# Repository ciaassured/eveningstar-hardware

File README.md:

# Eveningstar Hardware

Eveningstar is a gateway between a Morningstar MeterBus network and a standard Ethernet/IP network. It connects to the MeterBus port of a Morningstar solar charge controller or other compatible device, making the bus accessible over Ethernet for monitoring, automation, and control.

The hardware is built around an ESP32-C6 and divided into two galvanically isolated sections:

* A MeterBus interface, powered from the connected Morningstar device.
* An ESP32 and Ethernet interface, powered from its own DC input.

This isolation keeps the MeterBus network and the Morningstar device's ground separate from the rest of the system, which prevents ground loops through the MeterBus cable and stops fault currents from flowing across it. The ESP32 side can be powered from the same battery system as the charge controller or from a separate supply, even when the two operate at different voltages.

MeterBus communication is half-duplex and open-drain. The interface includes a Schmitt-trigger receive path and transient-voltage-suppression clamps to improve reliability when cables are routed through electrically noisy environments.

## Specifications

| | |
| --- | --- |
| Processor | ESP32-C6-WROOM-1-N8 module: Wi-Fi 6, Bluetooth LE, and IEEE 802.15.4, with 8 MB flash and an on-board antenna |
| Storage | 256 MB SPI NAND flash (GD5F2GM7) |
| Real-time clock | 32.768 kHz crystal |
| Ethernet | 10/100 Mbit/s, WIZnet W5500 with a hardware TCP/IP stack, RJ45 jack with integrated magnetics |
| MeterBus | RJ11 (6P6C) jack to the Morningstar MeterBus port |
| USB | USB-C to the ESP32-C6's native USB, for flashing, a serial console, and JTAG debugging; it does not power the board |
| Debug | Unpopulated 2.54 mm 2×3 header with serial, reset, and boot pins |
| Power input | 8–40 V DC through a 3.81 mm pluggable terminal block, ESP32 side |
| MeterBus supply | Powered by the Morningstar device through the MeterBus port, up to the 15.5 V Morningstar specifies, MeterBus side |
| Isolation | ISO6721 digital isolator between the two sides, rated 3000 V rms withstand and 450 V rms working voltage (basic isolation, UL 1577); only data crosses it |
| Operating temperature | −30 °C to +85 °C, from component ratings |
| Board size | 81.2 × 71.6 mm |

## Protection

* **Power input:** a 1 A fuse, a series Schottky diode against reverse polarity, and a 40 V TVS diode that clamps surges. The TVS diode sets the 40 V upper limit, well within the 80 V rating of the LMR38020S converter behind it.
* **Brown-out:** the ESP32 is held in reset until the converter reports that the 3.3 V rail is in regulation.
* **MeterBus:** galvanic isolation, since the MeterBus side is powered by the Morningstar device and shares no power or ground with the rest of the board. Its supply has a series Schottky diode against reverse polarity and a 17 V TVS diode, and the data line has a TVS clamp for positive and negative spikes.
* **USB:** ESD protection on the data lines. VBUS is not connected to any power rail, so the board cannot draw power from USB or feed power back into it.
* **Ethernet:** the jack's integrated magnetics transformer-couple the data pairs, and its shield is connected to ground only through a 1 nF, 2 kV capacitor, so the Ethernet cable carries no DC ground current.

The ratings above come from component datasheets. The board has not been independently tested or certified for isolation, surge immunity, or its temperature range.

## Installation

* **Power:** connect 8–40 V DC to the terminal block, observing the + and − markings on the bottom of the board. Add a Fuse the positive supply with a 1 A fuse close to the power source, and use wiring rated to carry at least 1 A continuously. This fuse protects the wiring in case of a short circuit. Choose a fuse that is appropriately rated for the system's voltages and currents.
* **MeterBus:** connect the RJ11 jack to the Morningstar device's MeterBus port using a standard straight through cable. The MeterBus side takes its power from that port. The outer two pins on each side of the 6P6C connector are shorted which means it is possible to use a four pin cable, but six pin is recommended.
* **Ethernet:** connect a standard Ethernet cable. The board is not powered over Ethernet. Note that this device does not support Auto-MDIX so a crossover cable may be needed in some cases if the other device also doesn't support auto Auto-MDIX.

> [!WARNING]
> Do not leave USB connected while the system is in service. USB ground is connected directly to the power input's negative terminal, so a connected USB host that is grounded elsewhere creates a second ground path. Current can then flow through the board's unfused ground and the USB cable, which can damage equipment or start a fire. Use USB only for flashing or debugging, and disconnect it afterwards.

## Debugging

### USB

The USB-C port connects straight to the ESP32-C6's native USB; there is no USB-to-serial chip in between. The chip's built-in USB Serial/JTAG controller gives a serial console, flashing, and JTAG debugging over one cable. The controller is part of the chip's hardware and is supported by its ROM bootloader, so it works on a blank module with no bootloader or firmware in flash, and the chip can enter download mode over USB by itself.

Firmware can still make the USB device disappear, by reconfiguring the USB pins, disabling the controller, or entering a sleep mode. If that happens, force the chip into its ROM download mode through the debug header, as below.

Remember that USB is for flashing and debugging only; see the warning under [Installation](#installation).

### Debug header

The unpopulated 2.54 mm 2×3 header, marked DEBUG, breaks out the ESP32's first serial port and its reset and boot pins:

| Pin | Label | Signal |
| --- | --- | --- |
| 1 | RST | ESP32 reset (EN), active low |
| 2 | 3V3 | Board 3.3 V rail, through jumper J_3V3 |
| 3 | TX | ESP32 UART0 transmit; connect to the adapter's receive |
| 4 | GND | Ground |
| 5 | RX | ESP32 UART0 receive; connect to the adapter's transmit |
| 6 | BOOT | ESP32 GPIO9; held low at reset, it enters ROM download mode |

Use it to flash over serial, including the bootloader, or to recover a board whose firmware has disabled native USB: hold BOOT low while releasing RST, and the chip starts in ROM download mode. Programmers that drive both pins can do this automatically.

When using the header, power the board with an external DC supply through its normal power input and on-board converter, and remove jumper J_3V3 so that the programmer's 3.3 V cannot backfeed the converter.

If the converter's power-good signal holds the reset line low while you are trying to flash or debug through the header, remove jumper J_RST as well; it connects the power-good signal to the ESP32's reset line.

J_3V3 and J_RST are 0603 0 Ω resistors beside the header, fitted at assembly and marked on the silkscreen.

## Resources

* Schematics, board drawings, 3D models, renders, and JLCPCB production files for the current hardware revision are attached to the [latest release](https://github.com/ciaassured/eveningstar-hardware/releases/latest).
* To order assembled boards, follow [`docs/jlcpcb_order.md`](docs/jlcpcb_order.md).
* Firmware is maintained separately in the [eveningstar-firmware](https://github.com/ciaassured/eveningstar-firmware) repository.
* The KiCad project and its build, review, and fabrication workflow are documented in [`pcb/README.md`](pcb/README.md).

## Disclaimer

This project is experimental and is not affiliated with or endorsed by Morningstar Corporation.

Use it at your own risk when interfacing with battery and solar equipment.

### AI Assistance

Portions of this project were created or modified using AI-assisted tools. AI-generated suggestions may be incomplete or incorrect and must not be treated as engineering certification.

Before manufacturing or using this hardware, independently review the schematics, PCB layout, component ratings, isolation boundaries, and fabrication outputs. Appropriate electrical, thermal, safety, and regulatory testing must also be performed.

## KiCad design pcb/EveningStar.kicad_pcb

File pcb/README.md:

# Eveningstar PCB

This directory contains the KiCad project for the Eveningstar PCB.

## Reproducibility Goal

The PCB should remain openable from this repository in the future, even if
external KiCad libraries, plugin indexes, vendor APIs, or downloaded data
sources disappear or change shape.

The rule of thumb is:

- Project-specific symbols, footprints, and 3D models should be committed under
  `pcb/lib`.
- Third-party libraries that are used by the board should be vendored into this
  repository, not referenced through a local KiCad plugin path.
- External tools are acceptable when they are sufficiently pinned and
  recoverable. KiCad itself is provided through the root Nix flake and locked by
  `flake.lock`.
- KiCad stock symbols are referenced through `KICAD_SYMBOL_DIR`, which is set by
  the Nix tooling to the flake-pinned KiCad package.

If a part needs local customization, copy the symbol, footprint, or model into a
project-owned library and reference that copy.

## Nix Workflow

The root flake owns the lock file and imports the PCB-specific Nix module from
`pcb/nix`. Use the flake from the repository root.

Open a shell with the pinned KiCad version:

```sh
nix develop
```

The dev shell includes KiCad plus the project helper scripts. Inside the shell,
the scripts are available as `eveningstar-*` commands.

Entering the development shell installs or updates the repo's pre-commit hook
for the current clone. It can also be installed explicitly from the shell:

```sh
lefthook install
```

Git does not automatically trust and execute hooks from cloned repositories.
Entering `nix develop` is the developer's explicit trust step: the shell uses
the Nix-provided Lefthook to sync `.git/hooks`, so Nix remains the only tooling
dependency. Lefthook then runs the same Nix-backed check suite used by CI.

## Checks

Run every automated check:

```sh
nix run .#checks
# or, inside nix develop:
eveningstar-checks
```

The aggregate command runs all checks even if an earlier one fails, then exits
non-zero if any failed. It is the entry point used by Lefthook and GitHub
Actions.

The individual checks remain available for diagnosing a failure.

### ERC and DRC

Run KiCad ERC and DRC, including warnings:

```sh
nix run .#drc
# or, inside nix develop:
eveningstar-drc
```

This writes `reports/erc.rpt` and `reports/drc.rpt`, prints both reports, and
exits non-zero if ERC or DRC reports violations.

### Repo-local KiCad references

Check for references to local, non-repo KiCad libraries or model paths:

```sh
nix run .#kicad-locality
# or, inside nix develop:
eveningstar-kicad-locality
```

This fails on absolute paths, KiCad third-party plugin variables, missing
repo-local 3D models, footprint library table entries outside `${KIPRJMOD}`, and
symbol library table entries outside `${KIPRJMOD}` or pinned `KICAD_SYMBOL_DIR`.

### Saved copper-zone fills

Check that every copper zone contains saved fill data on each of its layers:

```sh
nix run .#zones-filled
# or, inside nix develop:
eveningstar-zones-filled
```

After any board edit that can affect copper geometry, open the board in the
pinned KiCad PCB Editor, press <kbd>B</kbd> to refill all zones, and save before
committing. Production plotting uses the fills stored in the board, so this is
required even if DRC passes. The automated check detects absent saved fills; it
cannot prove that existing fills are current for the latest board edits.

### Vendored subtree drift

Check that the vendored JLCPCB subtree has not been edited directly:

```sh
nix run .#subtree-drift
# or, inside nix develop:
eveningstar-subtree-drift
```

This verifies `pcb/lib/JLCPCB-Kicad-Library` still matches the recorded subtree
squash commit and rejects uncommitted changes under that subtree.

## Publish Tools

Publish tools generate the complete artifact set for one hardware revision. They
are available through Nix, but are intentionally not run by Lefthook or CI.

Generate publish artifacts for the current checkout:

```sh
nix build --max-jobs auto .#publish
# or, to also link the result at reports/publish:
nix run .#publish
# inside nix develop:
eveningstar-publish
```

The output is exactly the set of GitHub release assets, in one flat directory
because releases hold no folders:

| File                         | Contents                                              |
| ---------------------------- | ----------------------------------------------------- |
| `EveningStar-gerbers.zip`    | Gerber and drill files for JLCPCB                     |
| `EveningStar-bom.csv`        | JLCPCB bill of materials                              |
| `EveningStar-cpl.csv`        | JLCPCB component placement list                       |
| `EveningStar-netlist.ipc`    | IPC-D-356 netlist for electrical test                 |
| `EveningStar-schematic.pdf`  | every schematic sheet                                 |
| `EveningStar-board.pdf`      | composite front and back views, then each layer       |
| `EveningStar-step.zip`       | STEP model of the assembled board, for enclosure CAD  |
| `EveningStar.glb`            | browser-optimized 3D model                            |
| `EveningStar-render-*.png`   | top, bottom, front, back, and isometric renders       |
| `EveningStar-turntable.webp` | the [turntable animation](#turntable-animation)       |
| `SHA256SUMS`                 | checksums of every other file                         |

Names carry no version, so `releases/latest/download/<name>` always links the
newest board, and the output depends only on the source rather than on the tag
it is released under. The production files are the `.#production` payload, which
uses the same names; the Toolkit's `designators.csv` is left out of both because
it only repeats the BOM. The per-sheet and per-layer SVGs are review artifacts
rather than release assets, built by `nix run .#review`.

`nix build` exposes the Nix store output through `result`; the command form also links that immutable output at
`reports/publish`. Because this is a derivation of the filtered PCB source and
pinned publishing tools, unchanged outputs are reused from the local Nix store
and can be shared through the configured Cachix cache. Release metadata and
changelog generation can be added to this same artifact contract without
changing the review workflow.

Generate only the JLCPCB production payload:

```sh
nix build .#production
# or, to also link the result at reports/production:
nix run .#production
# inside nix develop:
eveningstar-production
```

The production payload contains the Gerber/drill archive, BOM, placement list,
and IPC-D-356 netlist, under the same names as the GitHub release. Its settings
pin the Fabrication Toolkit 5.3.1 JLCPCB placement translations used for V1. The
build runs DRC and schematic-parity validation, then plots the zone fills
committed in the KiCad board without refilling them. Fill and save zones in the
pinned KiCad editor after relevant design changes; plotting the reviewed stored
fills avoids nondeterministic polygon decomposition between independent KiCad
processes. Project-specific corrections live as hidden `FT Rotation Offset`
fields on the affected KiCad footprints; update them only after checking
component pin 1 orientation against the datasheet and assembly preview. The
Toolkit's built-in rotations match footprint names by pattern, such as
`^SOT-23`, and are meant for KiCad's standard footprints, so EasyEDA-named
footprints that happen to match, such as D7's
`SOT-23-3_L3.0-W1.7-P0.95-LS2.9-BR`, carry a 180° offset that cancels them.
Through-hole parts are placed at the centre of their pads unless `FT Origin` is
`Anchor`, which RJ2 uses because JLCPCB's model for it sits on the footprint
anchor. U1's SOT-89 counts as through-hole because its tab has plated holes, so
it needs the same. Generated timestamps, ZIP entry metadata, permissions, and
file order are normalized for reproducible builds. The Toolkit source revision
is pinned by the root `flake.lock` alongside KiCad and the rest of the
toolchain. KiCad provides the underlying fabrication exporters; the pinned
Toolkit is retained for its JLCPCB-specific component-origin and rotation
translations and for compatibility with the production process used for the
original board.

Production files are build artifacts and are not committed. Local output is
ignored under `pcb/production` and `reports`; published manufacturing files
belong in the GitHub release for the exact source tag that produced them. The
original as-ordered files remain available from the historical `v1.0.0` tag.

To force a fresh build and have Nix compare it with the existing store output:

```sh
nix build .#production --rebuild
```

The aggregate is assembled from independent schematic-document, PCB-document,
plan-render, side-render, isometric-render, turntable-render, GLB, STEP, and
production derivations. Nix can schedule those components in parallel and reuse
them individually. They are also directly inspectable with commands such as
`nix build .#render-plan` or `nix build .#model-step`, without exposing
additional imperative applications.

### Turntable animation

Build the looping turntable animation used to showcase the board:

```sh
nix build --max-jobs auto .#render-turntable
```

That leaves the usual `result` symlink, which is a garbage-collection root, so
the animation is at `result/EveningStar-turntable.webp`. It is not committed:
`.#publish` carries it as `EveningStar-turntable.webp`, and
`nix run .#release` attaches it to the GitHub release, which the top-level
`README.md` embeds through the `releases/latest/download/` alias so the link
survives future releases untouched. Print the store path with
`nix build --print-out-paths` if something needs to consume the output without
relying on `result`.

The render is a chain of derivations of the filtered PCB source and the pinned
toolchain, each reused from the store, and shareable through Cachix, while its
inputs are unchanged:

| Package              | Produces                                              |
| -------------------- | ----------------------------------------------------- |
| `.#board-glb`        | the board as fitted, as an uncompressed kicad-cli GLB |
| `.#turntable-frames` | one PNG per frame, rendered from it by Cycles         |
| `.#render-turntable` | `EveningStar-turntable.webp`, encoded from the frames |

`.#model-glb`, the browser model in the release, is `.#board-glb` compressed
with `gltfpack`. Changing the render script re-renders the frames without
re-exporting the board, and changing the encoding re-encodes without rendering.

The board stands upright on its bottom edge, the way round it is drawn, leans
20°, and rides a turntable in front of a level, still camera, sweeping front
face to edge-on sliver to back face. The lean belongs to the board rather than
to the viewer, so it swings round with the spin: the component side is seen from
above, the bare copper side from below half a turn later, and the board rocks
from side to side through the edge-on quarters. Key, fill, and rim area lights
stay put while the board turns, so shadows sweep across it as they would in a
studio. The animation is 180 frames of a full revolution at a 33 ms frame delay,
so it runs at 30 fps and takes just under six seconds to come round. It is
encoded as an animated WebP with an alpha channel, so it sits on light and dark
README backgrounds alike.

`pcb/nix/scripts/turntable.py` runs inside Blender. Its options are the knobs:
`--tilt` (`20` reverses the lean), `--stand` to turn the board within its own
plane before it is stood up, `--frames`, `--width`, `--height`, `--fill`,
`--focal-length`, `--samples`, and `--mask-colour`. `--only` renders just the
listed frames, which is the quick way to try a change:

```sh
nix build .#board-glb
nix shell --inputs-from . nixpkgs#blender -c blender -b --factory-startup \
  --python-exit-code 1 -P pcb/nix/scripts/turntable.py -- \
  --model result/EveningStar.glb --output reports/turntable --only 0,45,90
```

At a 760x720 canvas the animation lands around 4.5 MB. The WebP settings live in
the `.#render-turntable` derivation. Quality 65 is already low enough that the
frames are visually indistinguishable from the PNGs, and method 6 took around
forty times longer than method 4 on one core for about 4% smaller output, so the
frame count and canvas size are where the remaining bytes are.

The camera distance is solved once from the geometry, so that the widest point
of the whole revolution reaches `--fill` of the canvas and the board stays the
same size in every frame. Every vertex rides a circle of radius r at height z
about the spin axis. Seen from distance D, it reaches at most r / sqrt(D² − r²)
across the frame and |z| / (D − r) up or down, each scaled by the lens, so the
maximum over the vertices bounds the continuous revolution exactly, and a
bisection on D lands it on the fill.

kicad-cli gives the board layers materials of their own, on meshes named
`<board>_soldermask`, `<board>_pad`, and so on, and the script sets those to a
coated mask in `--mask-colour`, gold pads and vias, white silkscreen, and FR4.
Component models carry only a colour through the export, so they arrive at
glTF's defaults of fully metallic and fully rough, which renders plastic as dull
metal. These models paint bare metal in light neutral colours up to pure white:
leads, terminals, the magjack and ESP32 shields, and the electrolytic's can,
some with a blue cast. The script makes those and gold-ish ones polished metal,
and the dark and strongly coloured rest plastic. Metal needs something to
mirror, so the world behind the transparent film is a studio backdrop, bright
overhead and dark underfoot. Do-not-populate parts are left out of the export.
The frames use Blender's AgX view transform with its punchy look, which keeps
the mask a deep blue and the plastics dark under studio lights.

Cycles renders on the CPU, since the build sandbox has no GPU, at 32 samples
with denoising, which came within 45 dB PSNR of 64 samples at well under two
thirds of the time. One Blender process uses every core Nix grants the build;
splitting the frames across several processes measured no faster. With a fixed
seed the frames are reproducible: two runs on the same machine render identical
pixels. On a 32-core machine the frames take about nine minutes. Blender's
closure is about 3.8 GB, fetched once from the binary cache.

The render used to be done by `kicad-cli pcb render`, which cannot keep lights
still while the board turns. It builds its own lights fixed to the board and
ignores any in its settings, so cast shadows stayed glued to the board while its
view-following camera light, which casts none, moved the shading. Its framing
also took probe renders, since it fits each image to the canvas individually and
zooms in perspective by moving the camera.

Because the animation is hosted rather than committed, a rebuild does not
disturb anything that is already published. Each release attaches the animation
rendered from its own source, so the README always shows the latest released
board.

Including the animation in `.#publish` adds about nine minutes to a
publish whenever the board has changed, more on machines with fewer cores. It is
not part of the review artifacts, so `nix run .#review` does not render it.

### Releases and hardware versioning

Release versions describe the hardware revision, not the volume or significance
of changes to the surrounding checks, rendering, review, or publishing tools.
Tooling-only changes do not normally require a hardware release.

- Increment the major version for an incompatible electrical, mechanical, or
  external-interface change.
- Increment the minor version for a backwards-compatible hardware capability or
  intentional circuit, component, or layout revision.
- Increment the patch version for corrections that preserve the intended
  circuit and interfaces, including fabrication-data, copper, keepout, and
  silkscreen fixes.

`v1.0.0` is a historical source tag and intentionally has no GitHub Release.
`v1.0.1` is the first release produced with the pinned, reproducible production
and publishing pipeline.

To prepare a release, first merge all intended changes to `main`, refill and
save copper zones after relevant board edits, and create a Markdown release
notes file. Review the changes and choose the version based primarily on the
schematics, board, and production outputs since the previous hardware tag:

```sh
nix run .#review -- v1.0.0 main
nix run .#release -- --dry-run v1.0.1 /path/to/release-notes.md
```

Inspect the rendered comparison and the staged assets under
`reports/release/v1.0.1/`. The dry run executes the complete checks and publish
build but does not create a tag or GitHub Release. When the result is ready to
publish, run:

```sh
nix run .#release -- v1.0.1 /path/to/release-notes.md
```

The release command requires a clean checkout of the latest `origin/main`,
rejects conflicting tags or releases, runs `nix run .#checks`, and builds the
full publish output locally. It checks that output against its `SHA256SUMS` and
stages it unchanged as the release assets; then it creates and pushes an
annotated tag and creates the GitHub Release. If GitHub release creation fails after the tag is pushed, correct the
problem and rerun the same command; an existing tag is accepted only when it
identifies the same `main` commit.

## Review Tools

Review tools generate artifacts for a human to inspect or compare. They are
available through Nix, but are intentionally not run by Lefthook or CI.

Generate a comparison from a pull request number or URL:

```sh
nix run .#review -- 31
# equivalent explicit form:
nix run .#review -- --pr 31
# URLs also work:
nix run .#review -- https://github.com/ciaassured/eveningstar-hardware/pull/31
# or, inside nix develop:
eveningstar-review 31
```

Compare any two locally available commits, branches, or tags by listing the
destination revision first and the source revision second:

```sh
nix run .#review -- v0.2.0 v0.3.0
nix run .#review -- main feature/new-layout
nix run .#review -- 2c5bf31 96e61e4
```

Compare a revision with the current working tree using `--worktree`. This
includes staged, unstaged, untracked, and deleted files, but excludes files
ignored by Git:

```sh
nix run .#review -- main --worktree
# HEAD is the default destination revision:
nix run .#review -- --worktree
```

For pull requests, the command resolves the exact source and destination
commits recorded by GitHub without changing or depending on the checkout. Git
revision comparisons archive the exact requested trees, while worktree
comparisons create an isolated temporary snapshot without switching branches or
modifying local files. Nix realizes the same publish derivation for either form.
Cached artifact sets are reused, then linked under
`reports/review` and compared through their browser-viewable SVG, PNG, and GLB
outputs. It serves the comparison on an ephemeral `127.0.0.1` port and prints
the URL; press Ctrl+C when the review is finished.
It also opens the URL in the default browser when a desktop opener is available;
the foreground server exits when interrupted and does not remain orphaned.
The view picker covers native vector schematic and board views, deterministic
KiCad 3D renders, and the interactive Three.js board model. Every view supports
overlay/reveal, side-by-side, pixel-difference, and highlighted-change modes.
Documents can be panned and zoomed without rasterizing SVGs; side-by-side
navigation can optionally be synchronized. Use <kbd>←</kbd> and <kbd>→</kbd> to
change view, <kbd>↑</kbd> and <kbd>↓</kbd> to change comparison mode, and
<kbd>[</kbd> and <kbd>]</kbd> to move through the current view's pages, layers,
images, or presets. Pull-request comparisons use `gh` for metadata and Git to
fetch missing commit objects; both are provided by Nix.

Generate the report without starting the local server:

```sh
nix run .#review -- --no-serve 31
nix run .#review -- --no-serve main --worktree
```

Because the review tool comes from the current checkout while the hardware
inputs come from the requested snapshots, a feature branch can test changes to
the review tooling against an existing PR or pair of revisions.

Artifacts are written under `reports/`.

## CI Checks

Pull requests to `main` run `.github/workflows/checks.yml`.

The workflow:

- Installs Nix.
- Optionally configures Cachix.
- Runs `nix run .#checks`, the same aggregate command used by Lefthook.
- Uploads ERC and DRC reports when they are generated.

The aggregate command attempts every check, so a failure in an earlier check
does not prevent ERC/DRC reports from being generated and uploaded.

## Library Layout

Vendored and project-owned libraries live under `pcb/lib`.

```text
pcb/lib/
  custom/
    custom_symbols.kicad_sym
  EasyEDA/
    EasyEDA.kicad_sym
    EasyEDA.pretty/
    EasyEDA.3dshapes/
  JLCPCB-Kicad-Library/
    symbols/
    footprints/
    3dmodels/
```

The KiCad library nicknames are kept stable in `sym-lib-table` and
`fp-lib-table`, so schematic references like `EasyEDA:...`,
`custom_symbols:...`, and `PCM_JLCPCB:...` remain readable.

## Development Plugins And Sources

This board has used external KiCad plugins and data sources during development:

- [ImpartGUI](https://github.com/Steffen-W/Import-LIB-KiCad-Plugin)
- [JLCPCB Fabrication Toolkit](https://github.com/bennymeg/Fabrication-Toolkit)
- [JLCPCB-Kicad-Library](https://github.com/CDFER/JLCPCB-Kicad-Library)

Those tools are useful if you are actively adding or updating parts, generating
fabrication outputs, or syncing vendor metadata. Someone working on the board
will probably want them installed in their interactive KiCad setup.

They should not be required just to open, check, or review the project. Any
symbols, footprints, or 3D models required by the board should be present in
this repository, and KiCad itself should be obtained through Nix.

## Adding Parts

When adding a part from a plugin or external source:

1. Add or copy the required symbol, footprint, and 3D model into `pcb/lib`.
2. Reference files through `${KIPRJMOD}/lib/...`, not through
   `${KICAD*_3RD_PARTY}`, absolute paths, or plugin cache paths.
3. Run `nix run .#checks`.

For the vendored JLCPCB subtree, do not edit files in
`pcb/lib/JLCPCB-Kicad-Library` directly. Update the subtree as a subtree, or
copy the asset into a project-owned library before customizing it.

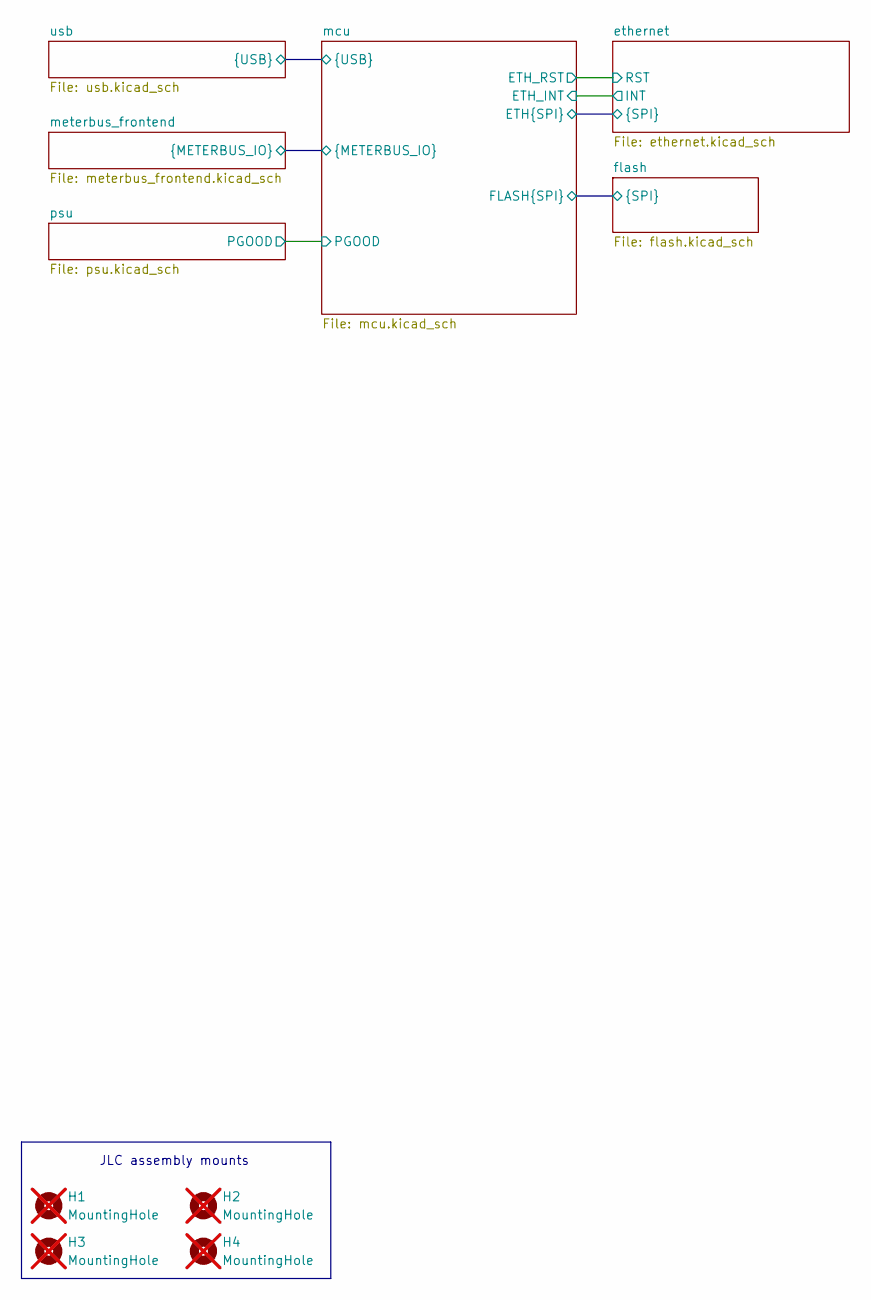
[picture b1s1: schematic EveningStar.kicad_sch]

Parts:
H1, H2, H3, H4: MountingHole; JLC_PCBA_Tooling_Mount; not fitted

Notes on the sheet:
JLC assembly mounts

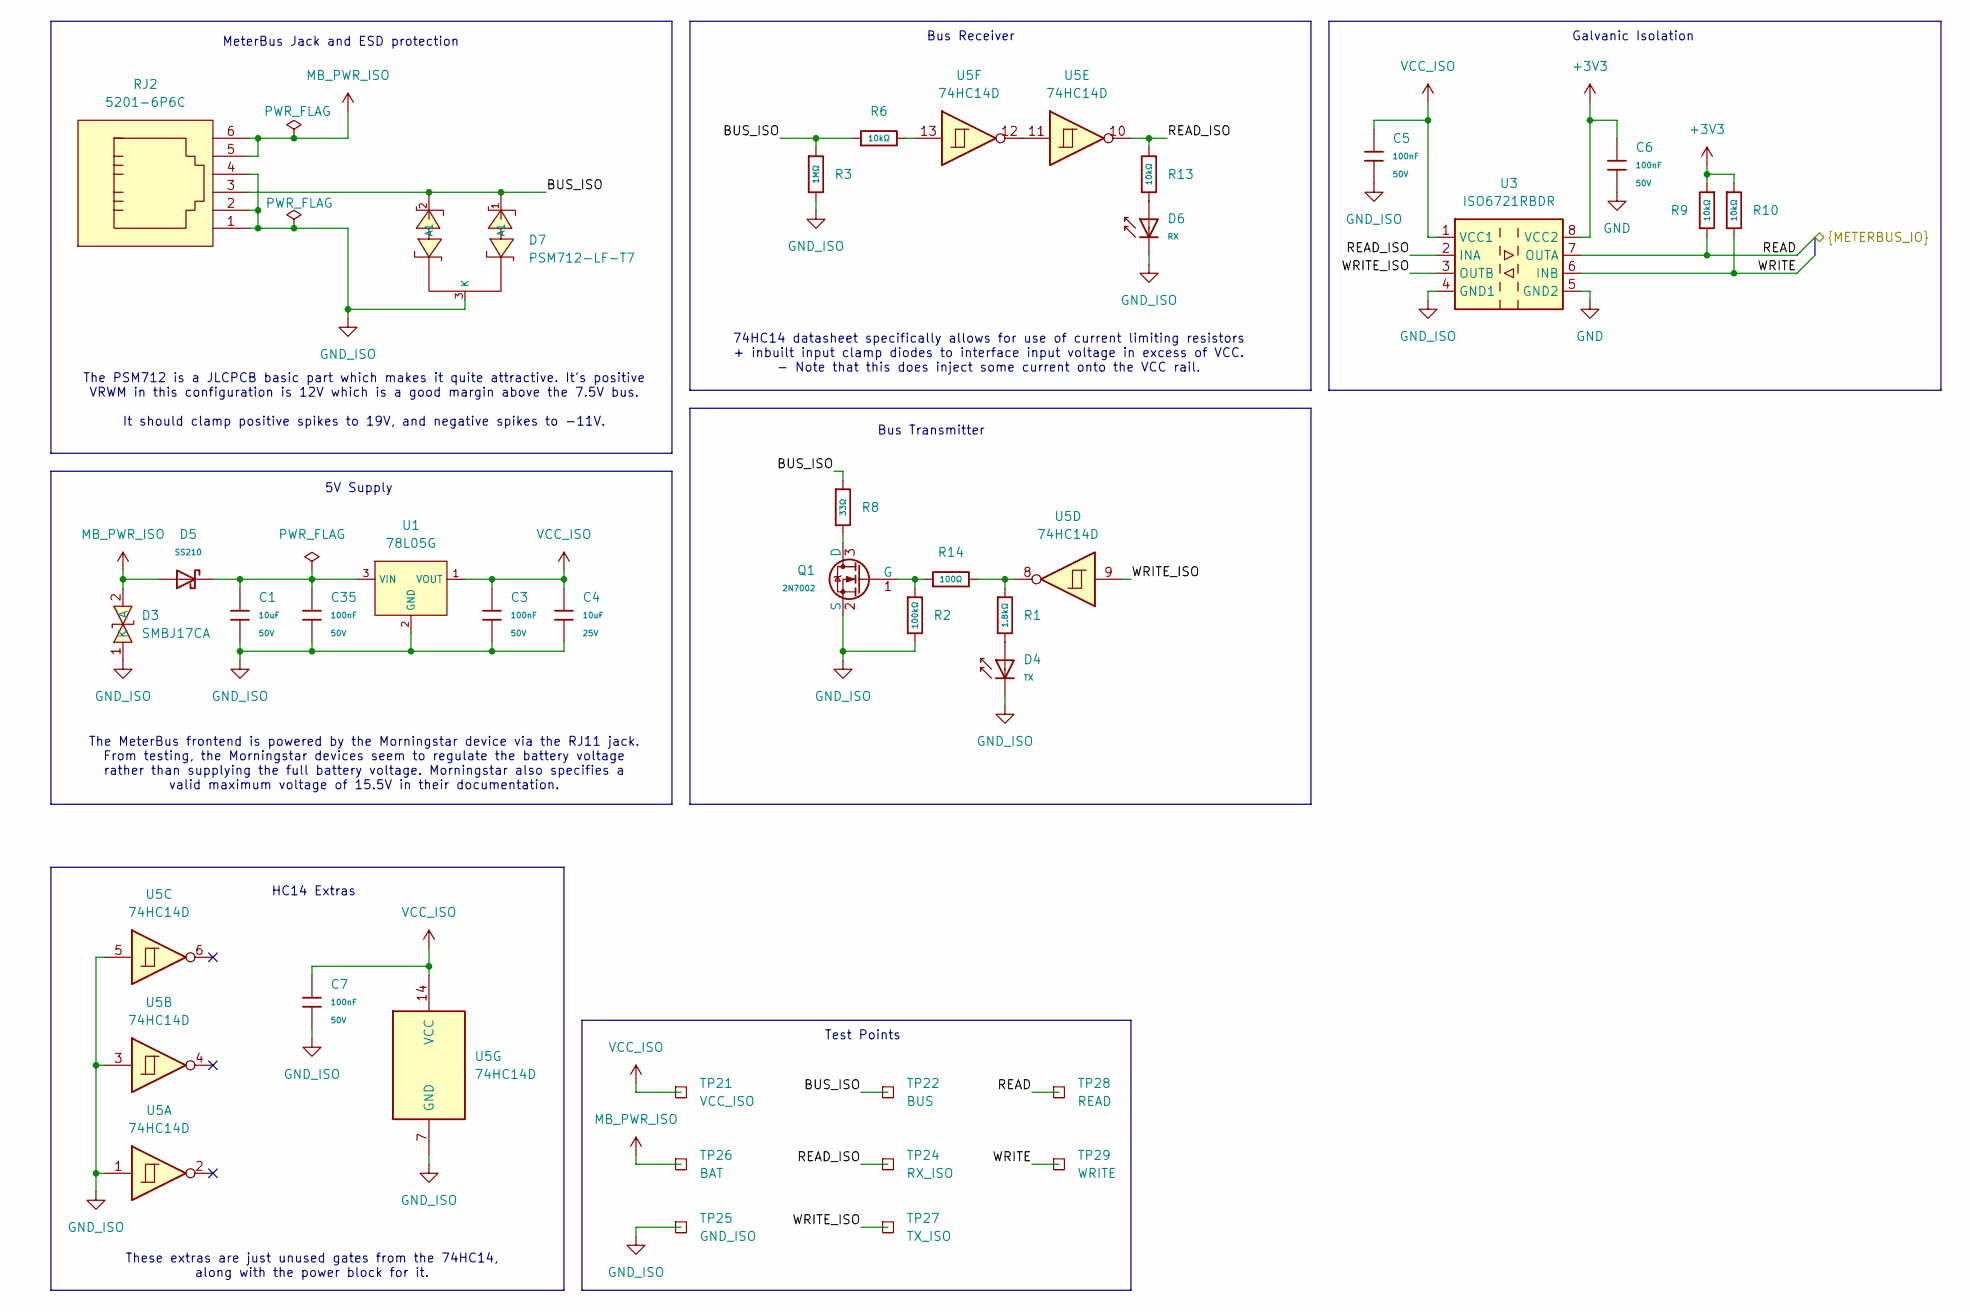
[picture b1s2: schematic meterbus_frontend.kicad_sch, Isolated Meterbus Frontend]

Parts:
C1: 10uF; C_1206; Voltage Rated 50V; Tolerance ±10%; Part CL31A106KBHNNNE; LCSC C13585
C3, C5, C6, C7, C35: 100nF; C_0603; Voltage Rated 50V; Tolerance ±10%; Part CC0603KRX7R9BB104; LCSC C14663
C4: 10uF; C_0603; Voltage Rated 25V; Tolerance ±20%; Part CL10A106MA8NRNC; LCSC C96446
D3: SMBJ17CA; SMB_L4.3-W3.6-LS5.4-BI; MPN SMBJ17CA; LCSC Part C3720411
D4: TX; D_0805; Forward Voltage (VF) 1.6V~2.6V; Part NCD0805R1; LCSC C84256
D5: SS210; D_SMA; Forward Voltage (Vf@If) 850mV@2A; Reverse Voltage (Vr) 100V; Part SS210; LCSC C14996
D6: RX; D_0805; Part KT-0805G; LCSC C2297
D7: PSM712-LF-T7; SOT-23-3_L3.0-W1.7-P0.95-LS2.9-BR; Breakdown Voltage 13.3V; Part PSM712-LF-T7; LCSC C32677
Q1: 2N7002; Q_SOT-23; Part 2N7002; LCSC C8545
R1: 1.8kΩ; R_0603; Overload Voltage (Max) 75V; Tolerance ±1%; Part 0603WAF1801T5E; LCSC C4177
R2: 100kΩ; R_0603; Overload Voltage (Max) 75V; Tolerance ±1%; Part 0603WAF1003T5E; LCSC C25803
R3: 1MΩ; R_0603; Overload Voltage (Max) 75V; Tolerance ±1%; Part 0603WAF1004T5E; LCSC C22935
R6, R9, R10, R13: 10kΩ; R_0603; Overload Voltage (Max) 75V; Tolerance ±1%; Part 0603WAF1002T5E; LCSC C25804
R8: 33Ω; R_0603; Overload Voltage (Max) 75V; Tolerance ±1%; Part 0603WAF330JT5E; LCSC C23140
R14: 100Ω; R_0603; Overload Voltage (Max) 75V; Tolerance ±1%; Part 0603WAF1000T5E; LCSC C22775
RJ2: 5201-6P6C; RJ45-TH_RRCH-5201-6P6C; MPN 5201-660111; LCSC Part C3097711
TP21: VCC_ISO; TestPoint_Pad_D1.0mm
TP22: BUS; TestPoint_Pad_D1.0mm
TP24: RX_ISO; TestPoint_Pad_D1.0mm
TP25: GND_ISO; TestPoint_Plated_Hole_D2.0mm
TP26: BAT; TestPoint_Plated_Hole_D2.0mm
TP27: TX_ISO; TestPoint_Pad_D1.0mm
TP28: READ; TestPoint_Pad_D1.0mm
TP29: WRITE; TestPoint_Pad_D1.0mm
U1: 78L05G; SOT-89-3_L4.5-W2.5-P1.50-LS4.2-BR; Output Voltage 5V; Dropout Voltage 1.7V@(40mA); Part 78L05G-AB3-R; LCSC C71136
U3: ISO6721RBDR; SOP-8_L4.9-W3.9-P1.27-LS6.0-BL_ISO6721RBDR; LCSC Part C5216401
U5: 74HC14D; SOIC-14_L8.7-W3.9-P1.27-LS6.0-BL; LCSC C5605

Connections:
+3V3: C6.1, R9.1, R10.1, U3.8 (VCC2); also elsewhere on the board
/mcu/READ: R9.2, TP28.1 (1_1), U3.7 (OUTA); also elsewhere on the board
/mcu/WRITE: R10.2, TP29.1 (1_1), U3.6 (INB); also elsewhere on the board
/meterbus_frontend/BUS_ISO: D7.1 (A1), D7.2 (A1), R3.1, R6.1, R8.1, RJ2.3, TP22.1 (1_1)
/meterbus_frontend/READ_ISO: R13.2, TP24.1 (1_1), U3.2 (INA), U5.10
/meterbus_frontend/WRITE_ISO: TP27.1 (1_1), U3.3 (OUTB), U5.9
GND: C6.2, U3.5 (GND2); also elsewhere on the board
GND_ISO: C1.2, C3.2, C4.2, C5.2, C7.2, C35.2, D3.1 (K), D4.1, D6.1, D7.3 (K), Q1.2 (S), R2.2, R3.2, RJ2.1, RJ2.2, RJ2.4, TP25.1 (1_1), U1.2 (GND), U3.4 (GND1), U5.1, U5.3, U5.5, U5.7 (GND)
MB_PWR_ISO: D3.2 (A), D5.2, RJ2.5, RJ2.6, TP26.1 (1_1)
unnamed: D4.2, R1.2
unnamed: D6.2, R13.1
unnamed: Q1.3 (D), R8.2
unnamed: Q1.1 (G), R2.1, R14.1
unnamed: R1.1, R14.2, U5.8
unnamed: R6.2, U5.13
unnamed: C1.1, C35.1, D5.1, U1.3 (VIN)
unnamed: U5.11, U5.12
VCC_ISO: C3.1, C4.1, C5.1, C7.1, TP21.1 (1_1), U1.1 (VOUT), U3.1 (VCC1), U5.14 (VCC)

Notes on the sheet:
74HC14 datasheet specifically allows for use of current limiting resistors + inbuilt input clamp diodes to interface input voltage in excess of VCC. - Note that this does inject some current onto the VCC rail.
Bus Transmitter
The PSM712 is a JLCPCB basic part which makes it quite attractive. It's positive VRWM in this configuration is 12V which is a good margin above the 7.5V bus. It should clamp positive spikes to 19V, and negative spikes to -11V.
Test Points
Galvanic Isolation
These extras are just unused gates from the 74HC14, along with the power block for it.
5V Supply
HC14 Extras
The MeterBus frontend is powered by the Morningstar device via the RJ11 jack. From testing, the Morningstar devices seem to regulate the battery voltage rather than supplying the full battery voltage. Morningstar also specifies a valid maximum voltage of 15.5V in their documentation.
MeterBus Jack and ESD protection
Bus Receiver

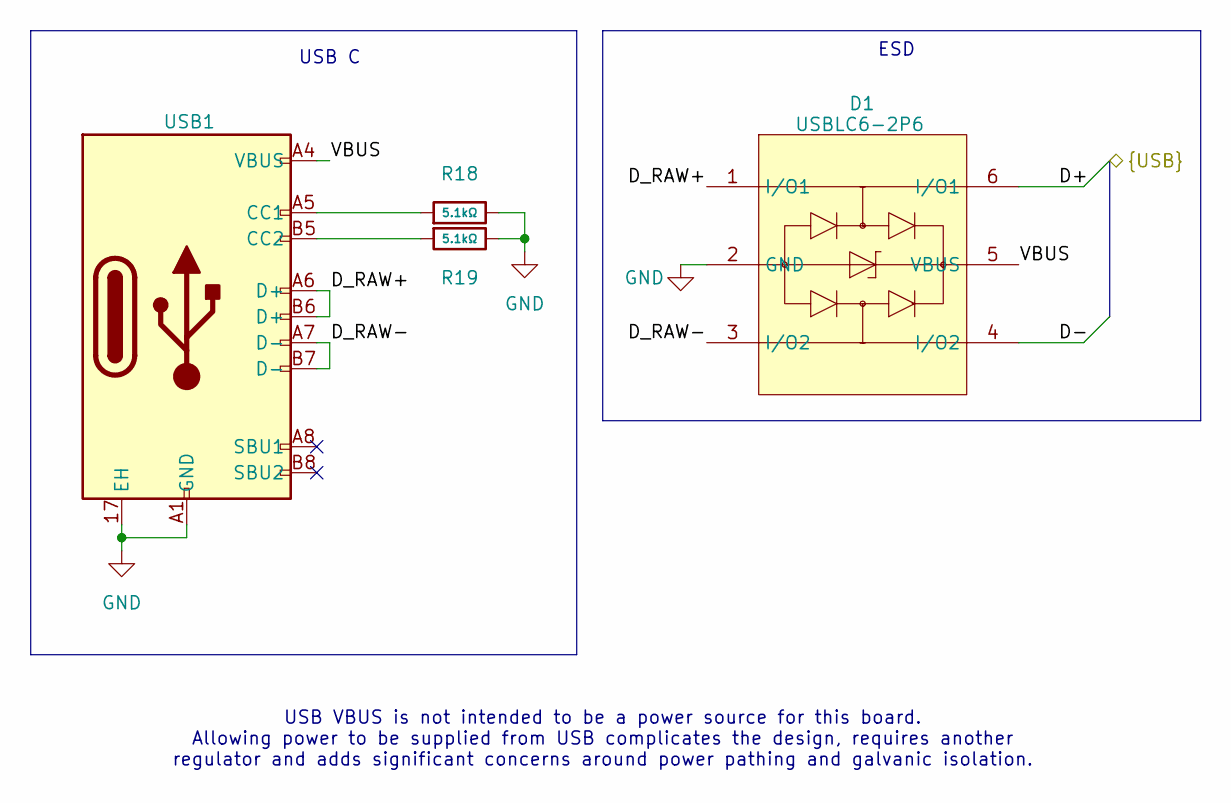
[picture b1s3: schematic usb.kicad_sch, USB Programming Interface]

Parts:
D1: USBLC6-2P6; SOT-666-6_L1.6-W1.2-P0.50-LS1.6-BR; MPN USBLC6-2P6; LCSC Part C15999
R18, R19: 5.1kΩ; R_0603; Overload Voltage (Max) 75V; Tolerance ±1%; Part 0603WAF5101T5E; LCSC C23186
USB1: GT-USB-7055BB; USB-C-TH_GT-USB-7055BB; MPN GT-USB-7055BB; LCSC Part C7450621

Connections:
/mcu/D+: D1.6 (I/O1); also elsewhere on the board
/mcu/D-: D1.4 (I/O2); also elsewhere on the board
/usb/D_RAW+: D1.1 (I/O1), USB1.A6 (D+), USB1.B6 (D+)
/usb/D_RAW-: D1.3 (I/O2), USB1.A7 (D-), USB1.B7 (D-)
/usb/VBUS: D1.5 (VBUS), USB1.A4 (VBUS), USB1.A9 (VBUS), USB1.B4 (VBUS), USB1.B9 (VBUS)
GND: D1.2 (GND), R18.2, R19.2, USB1.17 (EH), USB1.A1 (GND), USB1.A12 (GND), USB1.B1 (GND), USB1.B12 (GND); also elsewhere on the board
unnamed: R18.1, USB1.A5 (CC1)
unnamed: R19.1, USB1.B5 (CC2)

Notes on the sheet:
USB C
ESD
USB VBUS is not intended to be a power source for this board. Allowing power to be supplied from USB complicates the design, requires another regulator and adds significant concerns around power pathing and galvanic isolation.

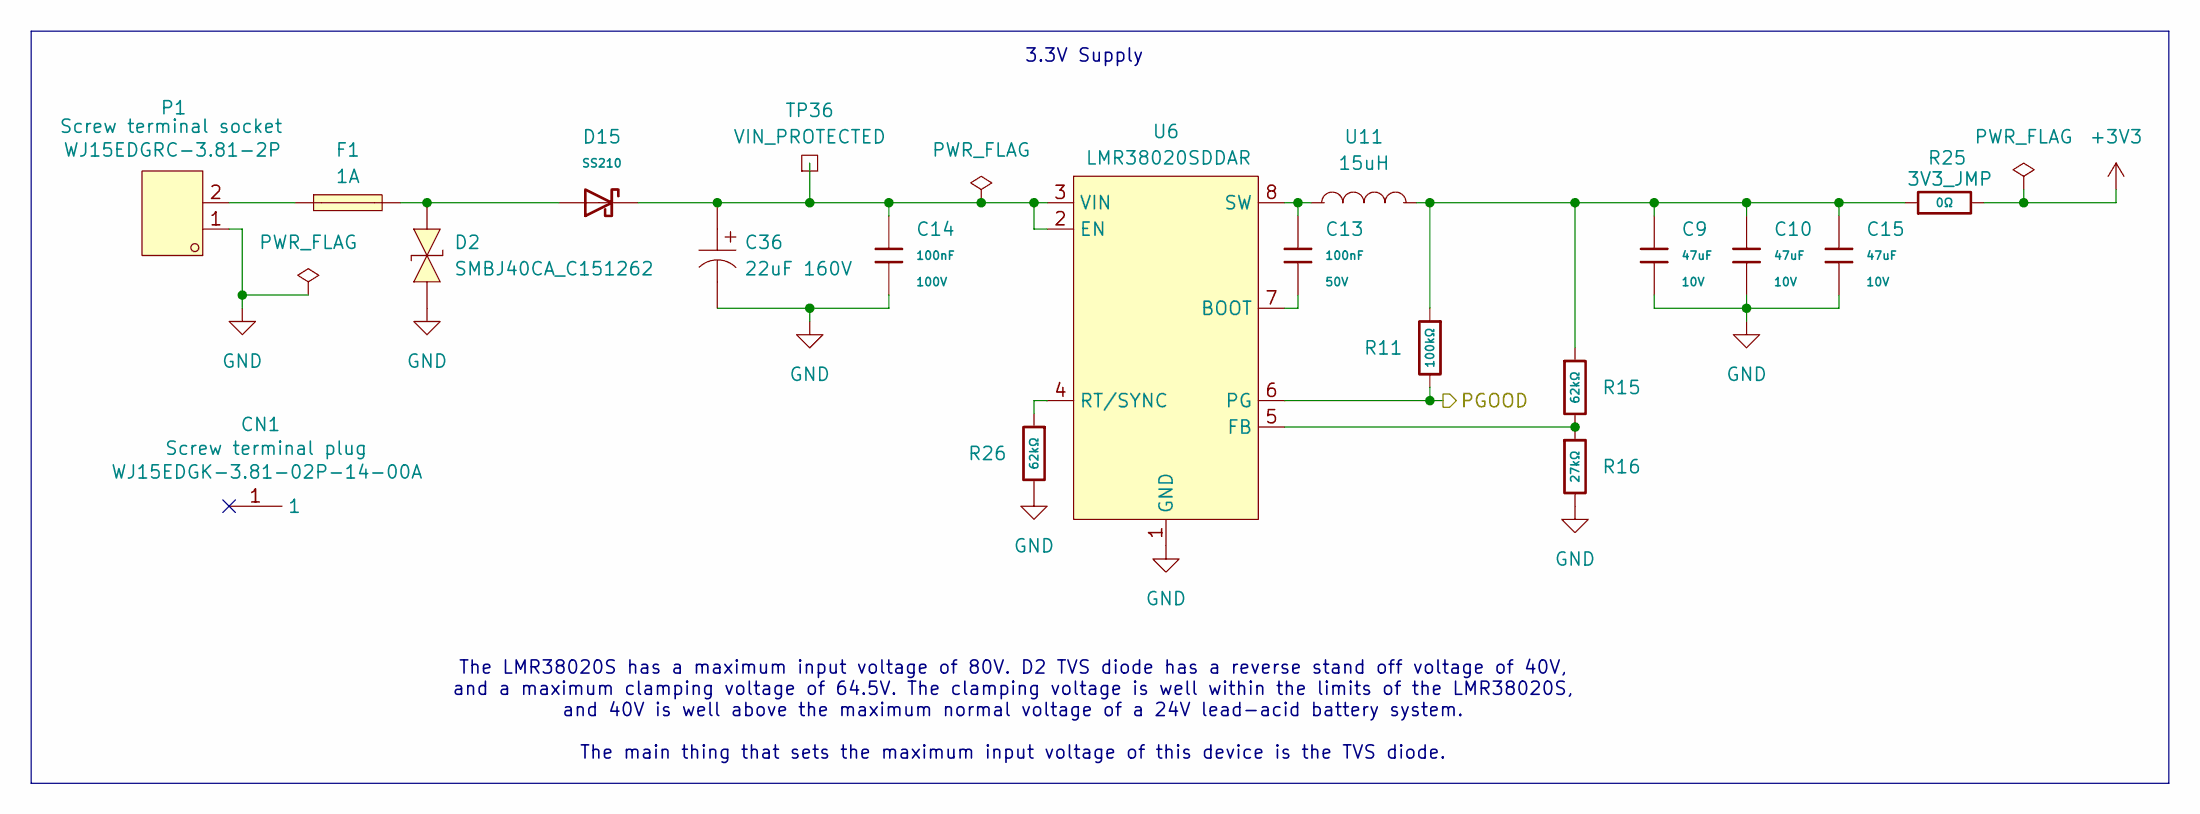
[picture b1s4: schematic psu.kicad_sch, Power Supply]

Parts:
C9, C10, C15: 47uF; C_1206; Voltage Rated 10V; Tolerance ±20%; Part CL31A476MPHNNNE; LCSC C96123
C13: 100nF; C_0603; Voltage Rated 50V; Tolerance ±10%; Part CC0603KRX7R9BB104; LCSC C14663
C14: 100nF; C_0805; Voltage Rated 100V; Tolerance ±10%; Part CL21B104KCFNNNE; LCSC C28233
C36: 22uF 160V; CAP-SMD_BD10.0-L10.3-W10.3-FD; MPN ULV2C220MNL1GS; LCSC Part C2164587
CN1: WJ15EDGK-3.81-02P-14-00A; FL_001; MPN WJ15EDGK-3.81-02P-14-00A; LCSC Part C8466
D2: SMBJ40CA_C151262; SMB_L4.6-W3.6-LS5.3-BI; MPN SMBJ40CA; LCSC Part C151262
D15: SS210; D_SMA; Forward Voltage (Vf@If) 850mV@2A; Reverse Voltage (Vr) 100V; Part SS210; LCSC C14996
F1: 1A; FUSE-SMD_L6.1-W2.6; MPN 0451001.MRL; LCSC Part C3099
P1: WJ15EDGRC-3.81-2P; CONN-TH_2P-P3.81_WJ15EDGRC-3.81-2P_CLIPPED; MPN WJ15EDGRC-3.81-02P-14-00A; LCSC Part C8387
R11: 100kΩ; R_0603; Overload Voltage (Max) 75V; Tolerance ±1%; Part 0603WAF1003T5E; LCSC C25803
R15, R26: 62kΩ; R_0603; Overload Voltage (Max) 75V; Tolerance ±1%; Part 0603WAF6202T5E; LCSC C23221
R16: 27kΩ; R_0603; Overload Voltage (Max) 75V; Tolerance ±1%; Part 0603WAF2702T5E; LCSC C22967
R25: 0Ω; R_0603; Overload Voltage (Max) 75V; Tolerance ±1%; Part 0603WAF0000T5E; LCSC C21189
TP36: VIN_PROTECTED; TestPoint_Plated_Hole_D2.0mm
U6: LMR38020SDDAR; ESOP-8_L4.9-W3.9-P1.27-LS6.0-BL-EP-1; MPN LMR38020SDDAR; LCSC Part C3192337
U11: 15uH; IND-SMD_L7.1-W6.6; MPN APH0630T150M; LCSC Part C5349699

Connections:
+3V3: R25.2; also elsewhere on the board
/mcu/PGOOD: R11.2, U6.6 (PG); also elsewhere on the board
GND: C9.2, C10.2, C14.2, C15.2, C36.2, D2.1 (K), P1.1, R16.2, R26.2, U6.1 (GND), U6.9 (GND); also elsewhere on the board
unnamed: C9.1, C10.1, C15.1, R11.1, R15.1, R25.1, U11.2
unnamed: D2.2 (A), D15.2, F1.2
unnamed: F1.1, P1.2
unnamed: C13.2, U6.7 (BOOT)
unnamed: C14.1, C36.1, D15.1, TP36.1 (1_1), U6.2 (EN), U6.3 (VIN)
unnamed: R15.2, R16.1, U6.5 (FB)
unnamed: R26.1, U6.4 (RT/SYNC)
unnamed: C13.1, U6.8 (SW), U11.1

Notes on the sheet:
The LMR38020S has a maximum input voltage of 80V. D2 TVS diode has a reverse stand off voltage of 40V, and a maximum clamping voltage of 64.5V. The clamping voltage is well within the limits of the LMR38020S, and 40V is well above the maximum normal voltage of a 24V lead-acid battery system. The ma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
3.3V Supply

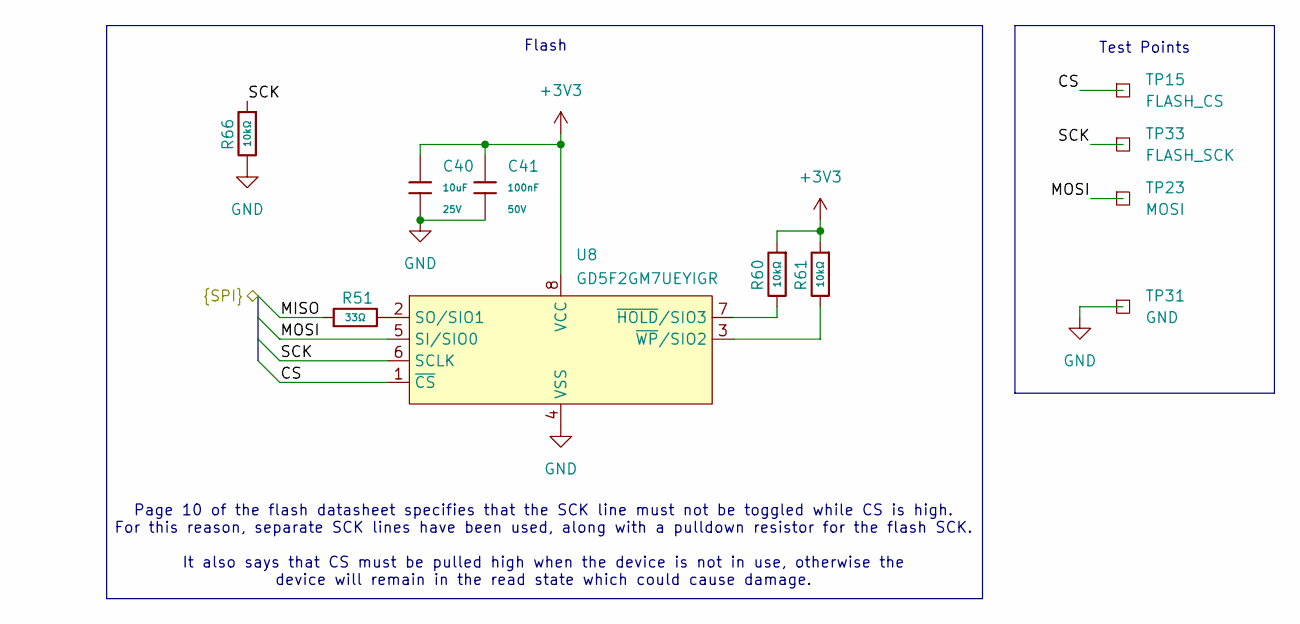
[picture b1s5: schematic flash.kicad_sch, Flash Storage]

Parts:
C40: 10uF; C_0603; Voltage Rated 25V; Tolerance ±20%; Part CL10A106MA8NRNC; LCSC C96446
C41: 100nF; C_0603; Voltage Rated 50V; Tolerance ±10%; Part CC0603KRX7R9BB104; LCSC C14663
R51: 33Ω; R_0603; Overload Voltage (Max) 75V; Tolerance ±1%; Part 0603WAF330JT5E; LCSC C23140
R60, R61, R66: 10kΩ; R_0603; Overload Voltage (Max) 75V; Tolerance ±1%; Part 0603WAF1002T5E; LCSC C25804
TP15: FLASH_CS; TestPoint_Pad_D1.0mm
TP23: MOSI; TestPoint_Pad_D1.0mm
TP31: GND; TestPoint_Plated_Hole_D2.0mm
TP33: FLASH_SCK; TestPoint_Pad_D1.0mm
U8: GD5F2GM7UEYIGR; WSON-8_L8.0-W6.0-P1.27-TL-1; MPN GD5F2GM7UEYIGR; LCSC Part C22412867

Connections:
+3V3: C40.2, C41.1, R60.1, R61.1, U8.8 (VCC); also elsewhere on the board
/flash/CS: TP15.1 (1_1), U8.1 (~CS); also elsewhere on the board
/flash/MISO: R51.1; also elsewhere on the board
/flash/MOSI: TP23.1 (1_1), U8.5 (SI/SIO0); also elsewhere on the board
/flash/SCK: R66.1, TP33.1 (1_1), U8.6 (SCLK); also elsewhere on the board
GND: C40.1, C41.2, R66.2, TP31.1 (1_1), U8.4 (VSS); also elsewhere on the board
unnamed: R51.2, U8.2 (SO/SIO1)
unnamed: R60.2, U8.7 (~HOLD/SIO3)
unnamed: R61.2, U8.3 (~WP/SIO2)

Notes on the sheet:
Page 10 of the flash datasheet specifies that the SCK line must not be toggled while CS is high. For this reason, separate SCK lines have been used, along with a pulldown resistor for the flash SCK. It also says that CS must be pulled high when the device is not in use, otherwise the device will re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
Test Points
Flash
